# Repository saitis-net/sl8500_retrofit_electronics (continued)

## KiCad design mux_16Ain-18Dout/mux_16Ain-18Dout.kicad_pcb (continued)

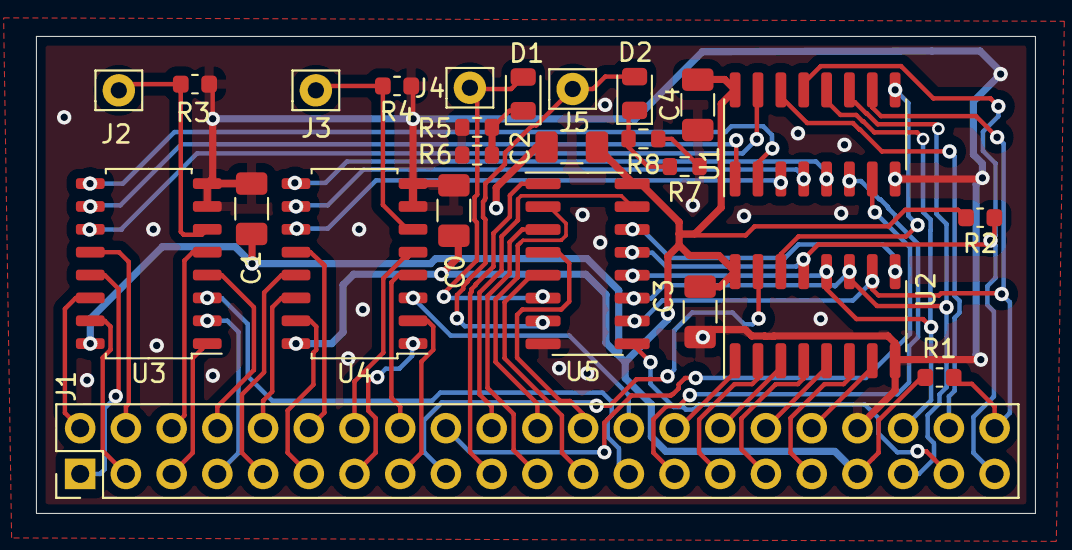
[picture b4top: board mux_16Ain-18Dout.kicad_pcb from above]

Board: 2 copper layers, 55.5 x 26.5 mm, 25 parts (0 on the bottom side), 56 nets.

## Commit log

2025-10-16 work on the sensor/legacy barcode scanner connector
2025-10-30 updated order detail for BDCLC controllers, received working controllers from JLC
2025-11-01 Work on re-using head flat cable, to avoid adding cable between MB and HEAD
2025-12-07 PCB calibration marker ready to order
2026-01-20 added 2.5 hdd box
2026-01-21 added .gitignore
2026-01-21 cleaning
2026-01-23 2.5-hdd_box: cut on bottom for usb-sata board, better placement of soldier pads
2026-01-28 Cosmetic changes
2026-02-03 height error on side corrected, cosmetics
2026-03-03 last order has small mistakes, this one should be better. Other things added, your responsibility to discover
2026-03-27 small correction for last order
